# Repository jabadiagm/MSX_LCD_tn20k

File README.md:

# MSX_LCD_tn20k
LCD cartridge for MSX1

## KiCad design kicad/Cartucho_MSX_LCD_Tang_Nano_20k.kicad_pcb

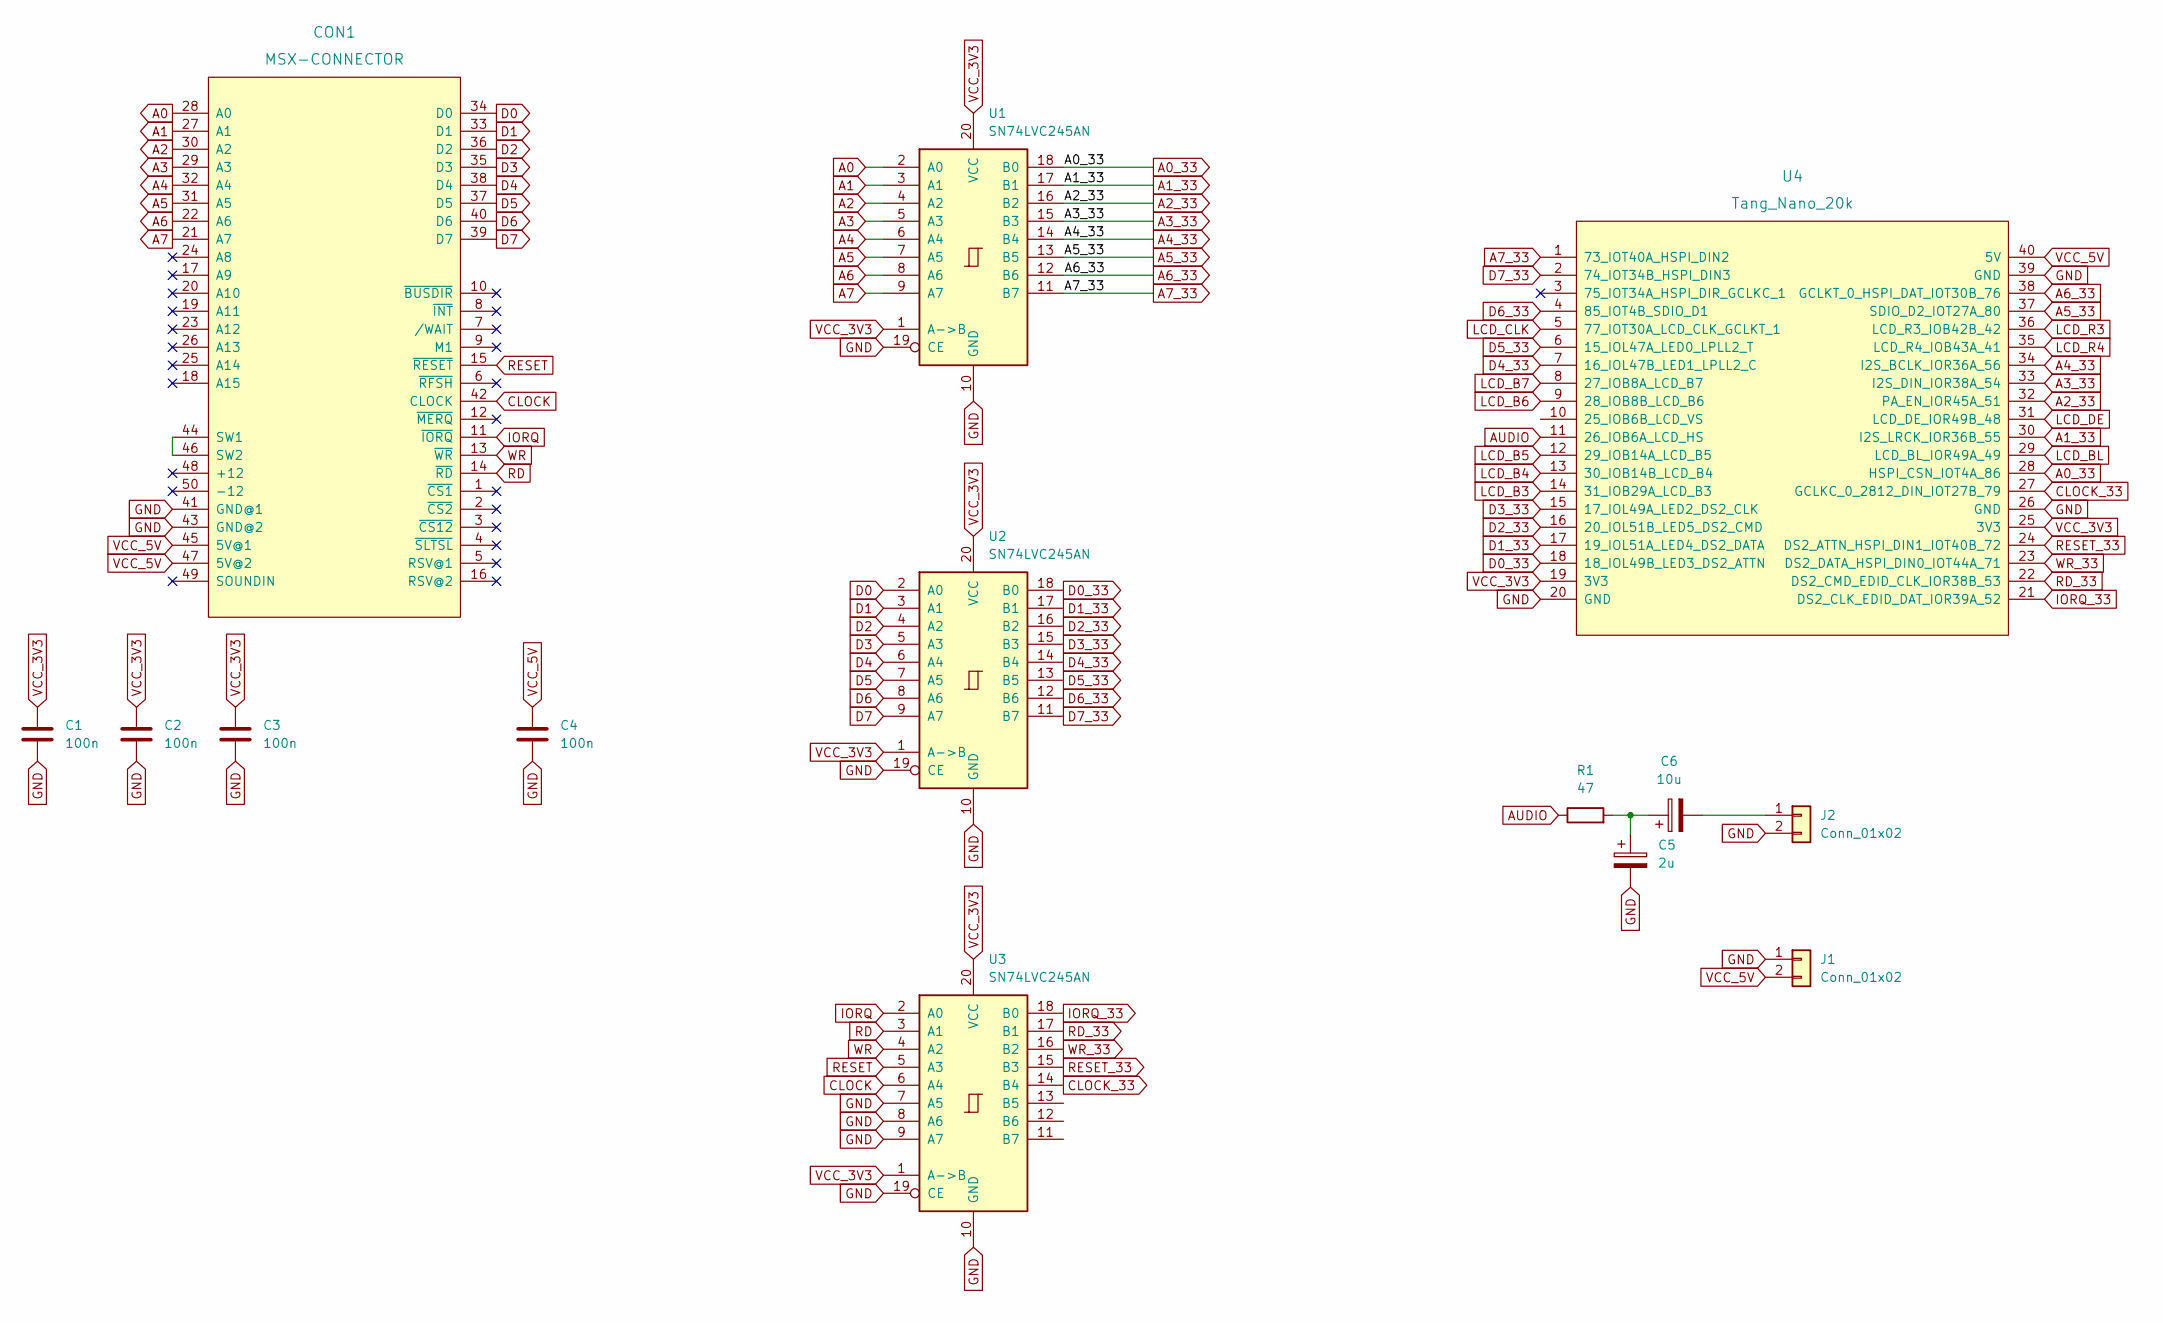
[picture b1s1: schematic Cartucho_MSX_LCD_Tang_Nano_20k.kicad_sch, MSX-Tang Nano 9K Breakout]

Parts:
C1, C2, C3, C4: 100n; C_Disc_D4.3mm_W1.9mm_P5.00mm
C5: 2u; CP_Radial_D4.0mm_P2.00mm
C6: 10u; CP_Radial_D4.0mm_P2.00mm
CON1: MSX-CONNECTOR; CARTRIDGE_MSX_LCD
J1, J2: Conn_01x02; PinHeader_1x02_P2.54mm_Horizontal
R1: 47; R_Axial_DIN0207_L6.3mm_D2.5mm_P7.62mm_Horizontal
U1, U2, U3: SN74LVC245AN; DIP-20_W7.62mm_LongPads
U4: Tang_Nano_20k

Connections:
A0: CON1.28 (A0), U1.2 (A0)
A0_33: U1.18 (B0), U4.28 (HSPI_CSN_IOT4A_86)
A1: CON1.27 (A1), U1.3 (A1)
A1_33: U1.17 (B1), U4.30 (I2S_LRCK_IOR36B_55)
A2: CON1.30 (A2), U1.4 (A2)
A2_33: U1.16 (B2), U4.32 (PA_EN_IOR45A_51)
A3: CON1.29 (A3), U1.5 (A3)
A3_33: U1.15 (B3), U4.33 (I2S_DIN_IOR38A_54)
A4: CON1.32 (A4), U1.6 (A4)
A4_33: U1.14 (B4), U4.34 (I2S_BCLK_IOR36A_56)
A5: CON1.31 (A5), U1.7 (A5)
A5_33: U1.13 (B5), U4.37 (SDIO_D2_IOT27A_80)
A6: CON1.22 (A6), U1.8 (A6)
A6_33: U1.12 (B6), U4.38 (GCLKT_0_HSPI_DAT_IOT30B_76)
A7: CON1.21 (A7), U1.9 (A7)
A7_33: U1.11 (B7), U4.1 (73_IOT40A_HSPI_DIN2)
AUDIO: R1.1, U4.11 (26_IOB6A_LCD_HS)
CLOCK: CON1.42 (CLOCK), U3.6 (A4)
CLOCK_33: U3.14 (B4), U4.27 (GCLKC_0_2812_DIN_IOT27B_79)
D0: CON1.34 (D0), U2.2 (A0)
D0_33: U2.18 (B0), U4.18 (18_IOL49B_LED3_DS2_ATTN)
D1: CON1.33 (D1), U2.3 (A1)
D1_33: U2.17 (B1), U4.17 (19_IOL51A_LED4_DS2_DATA)
D2: CON1.36 (D2), U2.4 (A2)
D2_33: U2.16 (B2), U4.16 (20_IOL51B_LED5_DS2_CMD)
D3: CON1.35 (D3), U2.5 (A3)
D3_33: U2.15 (B3), U4.15 (17_IOL49A_LED2_DS2_CLK)
D4: CON1.38 (D4), U2.6 (A4)
D4_33: U2.14 (B4), U4.7 (16_IOL47B_LED1_LPLL2_C)
D5: CON1.37 (D5), U2.7 (A5)
D5_33: U2.13 (B5), U4.6 (15_IOL47A_LED0_LPLL2_T)
D6: CON1.40 (D6), U2.8 (A6)
D6_33: U2.12 (B6), U4.4 (85_IOT4B_SDIO_D1)
D7: CON1.39 (D7), U2.9 (A7)
D7_33: U2.11 (B7), U4.2 (74_IOT34B_HSPI_DIN3)
GND: C1.2, C2.2, C3.2, C4.2, C5.2, CON1.41 (GND@1), CON1.43 (GND@2), J1.1, J2.2, U1.10 (GND), U1.19 (CE), U2.10 (GND), U2.19 (CE), U3.7 (A5), U3.8 (A6), U3.9 (A7), U3.10 (GND), U3.19 (CE), U4.20 (GND), U4.26 (GND), U4.39 (GND)
IORQ: CON1.11 (~IORQ), U3.2 (A0)
IORQ_33: U3.18 (B0), U4.21 (DS2_CLK_EDID_DAT_IOR39A_52)
LCD_B3: U4.14 (31_IOB29A_LCD_B3)
LCD_B4: U4.13 (30_IOB14B_LCD_B4)
LCD_B5: U4.12 (29_IOB14A_LCD_B5)
LCD_B6: U4.9 (28_IOB8B_LCD_B6)
LCD_B7: U4.8 (27_IOB8A_LCD_B7)
LCD_BL: U4.29 (LCD_BL_IOR49A_49)
LCD_CLK: U4.5 (77_IOT30A_LCD_CLK_GCLKT_1)
LCD_DE: U4.31 (LCD_DE_IOR49B_48)
LCD_R3: U4.36 (LCD_R3_IOB42B_42)
LCD_R4: U4.35 (LCD_R4_IOB43A_41)
unnamed: C5.1, C6.1, R1.2
unnamed: C6.2, J2.1
unnamed: CON1.44 (SW1), CON1.46 (SW2)
RD: CON1.14 (~RD), U3.3 (A1)
RD_33: U3.17 (B1), U4.22 (DS2_CMD_EDID_CLK_IOR38B_53)
RESET: CON1.15 (~RESET), U3.5 (A3)
RESET_33: U3.15 (B3), U4.24 (DS2_ATTN_HSPI_DIN1_IOT40B_72)
VCC_3V3: C1.1, C2.1, C3.1, U1.1 (A->B), U1.20 (VCC), U2.1 (A->B), U2.20 (VCC), U3.1 (A->B), U3.20 (VCC), U4.19 (3V3), U4.25 (3V3)
VCC_5V: C4.1, CON1.45 (5V@1), CON1.47 (5V@2), J1.2, U4.40 (5V)
WR: CON1.13 (~WR), U3.4 (A2)
WR_33: U3.16 (B2), U4.23 (DS2_DATA_HSPI_DIN0_IOT44A_71)

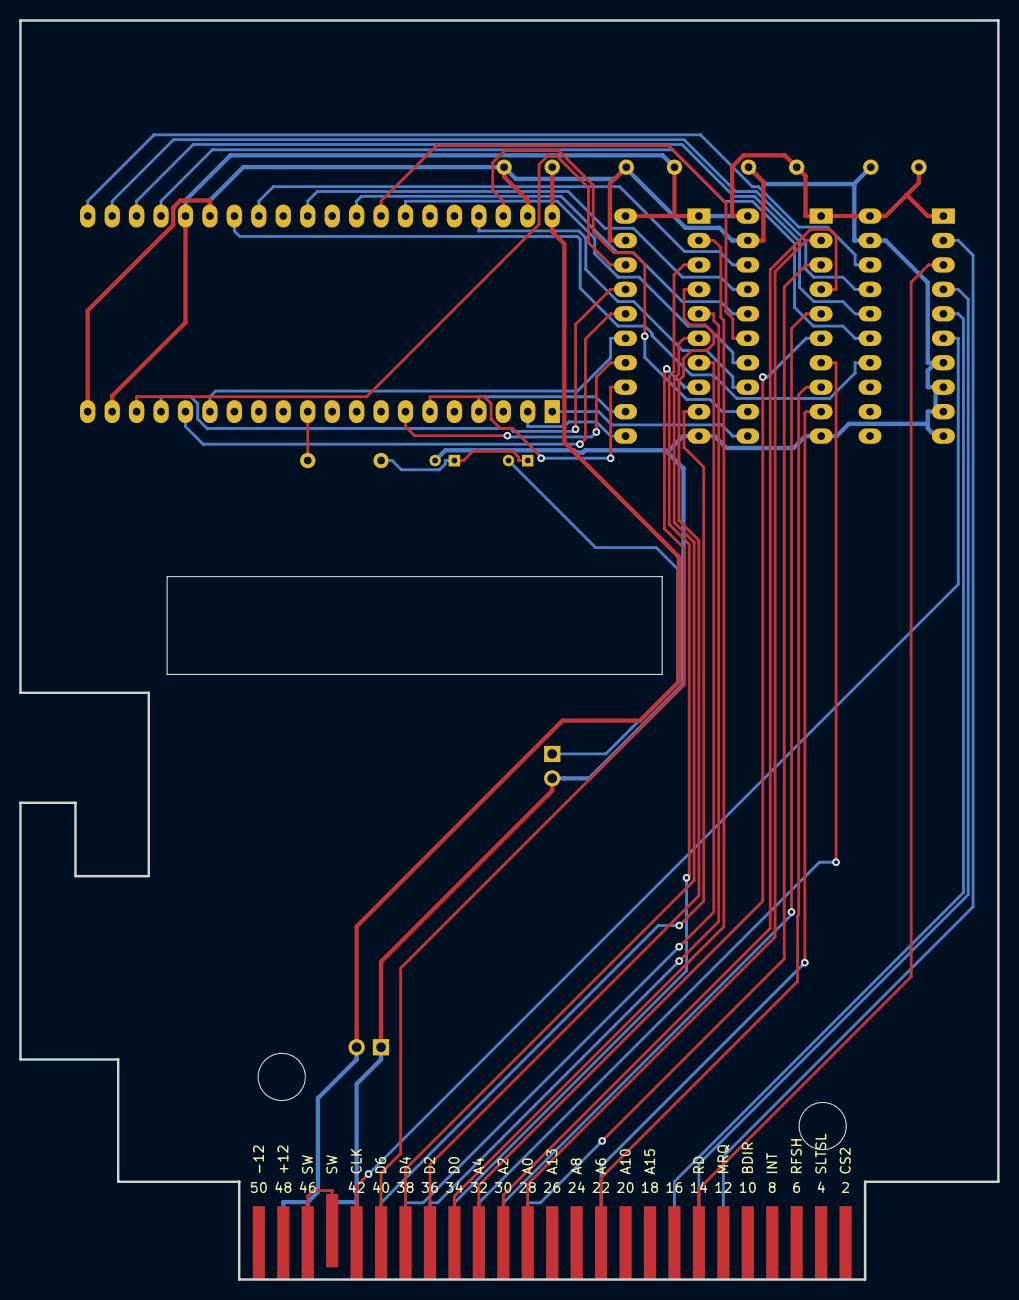
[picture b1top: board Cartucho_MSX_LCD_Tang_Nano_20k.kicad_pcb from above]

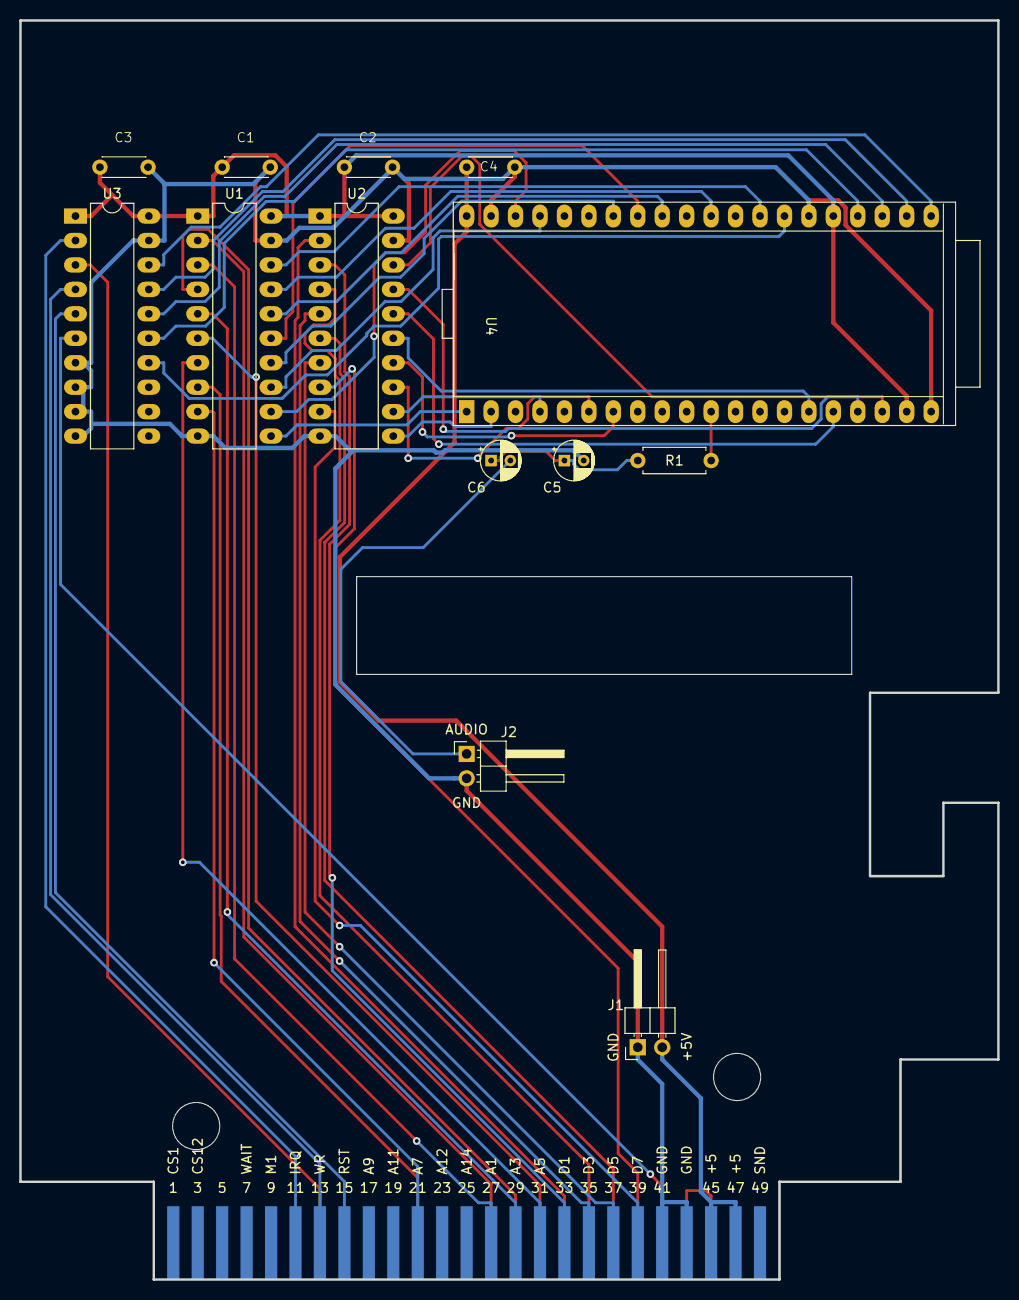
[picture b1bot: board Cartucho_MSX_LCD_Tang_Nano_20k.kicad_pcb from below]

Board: 2 copper layers, 101.6 x 130.8 mm, 14 parts (13 on the bottom side), 49 nets.

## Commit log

2024-04-28 Inicial
